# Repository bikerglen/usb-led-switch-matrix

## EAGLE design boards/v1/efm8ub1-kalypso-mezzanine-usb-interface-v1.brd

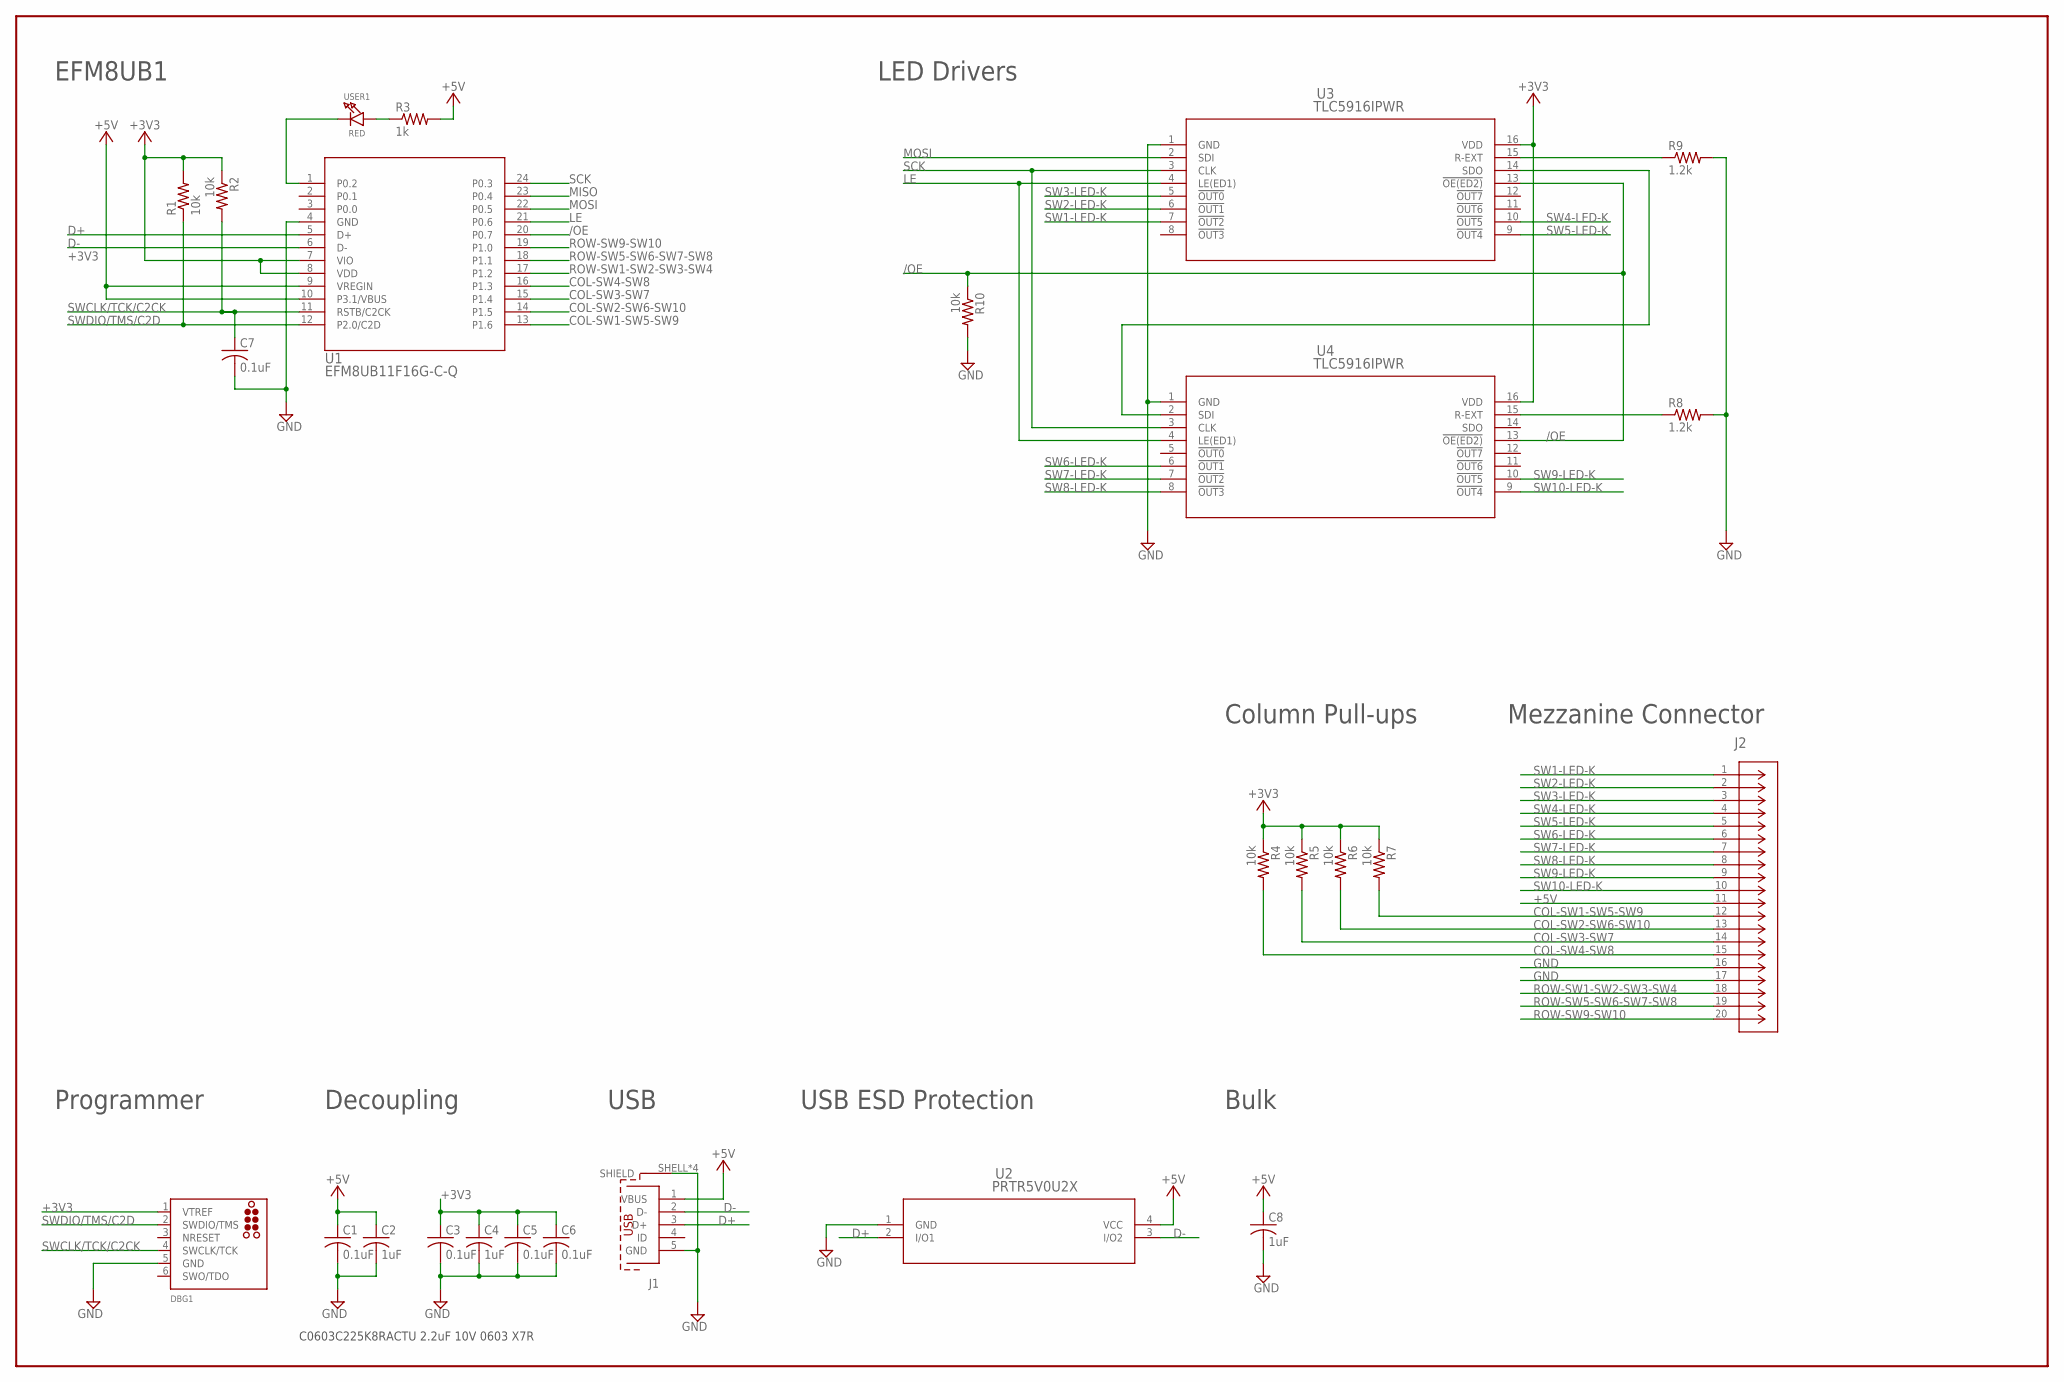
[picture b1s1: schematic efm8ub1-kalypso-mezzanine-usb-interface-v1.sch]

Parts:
C1, C3, C5, C6, C7: 0.1uF; C0603
C2, C4: 1uF; C0603
C8: 1uF; C1210
DBG1: TC2030-CTX-SWD; TC2030-MCP-NL
J1: 629105136821
J2: SLW20S-1C7LF; CON20_1X20_UB_58JF_GLE
R1, R2, R4, R5, R6, R7, R10: 10k; R0603
R3: 1k; R0603
R8, R9: 1.2k; R0603
U1: EFM8UB11F16G-C-Q; QSOP24
U2: PRTR5V0U2X; SOT143B
U3, U4: TLC5916IPWR; PW16_TEX
USER1: RED; CHIPLED_0805_NOOUTLINE

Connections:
+3V3: C3.1, C4.1, C5.1, C6.1, DBG1.1 (VTREF), R1.2, R2.1, R4.1, R5.1, R6.1, R7.1, U1.7 (VIO), U1.8 (VDD), U3.16 (VDD), U4.16 (VDD)
+5V: C1.1, C2.1, C8.1, J1.1 (VBUS), J2.11, R3.2, U1.9 (VREGIN), U1.10 (P3.1/VBUS), U2.4 (VCC)
/OE: R10.1, U1.20 (P0.7), U3.13 (!OE(ED2)), U4.13 (!OE(ED2))
COL-SW1-SW5-SW9: J2.12, R7.2, U1.13 (P1.6)
COL-SW2-SW6-SW10: J2.13, R6.2, U1.14 (P1.5)
COL-SW3-SW7: J2.14, R5.2, U1.15 (P1.4)
COL-SW4-SW8: J2.15, R4.2, U1.16 (P1.3)
D+: J1.3 (D+), U1.5 (D+), U2.2 (I/O1)
D-: J1.2 (D-), U1.6 (D-), U2.3 (I/O2)
GND: C1.2, C2.2, C3.2, C4.2, C5.2, C6.2, C7.2, C8.2, DBG1.5 (GND), J1.5 (GND), J1.SHELL (SHIELD), J1.SHELL1 (SHIELD), J1.SHELL2 (SHIELD), J1.SHELL3 (SHIELD), J2.16, J2.17, R8.2, R9.2, R10.2, U1.4 (GND), U2.1 (GND), U3.1 (GND), U4.1 (GND)
LE: U1.21 (P0.6), U3.4 (LE(ED1)), U4.4 (LE(ED1))
MISO: U1.23 (P0.4)
MOSI: U1.22 (P0.5), U3.2 (SDI)
unnamed: R3.1, USER1.A
unnamed: U3.14 (SDO), U4.2 (SDI)
unnamed: R8.1, U4.15 (R-EXT)
unnamed: R9.1, U3.15 (R-EXT)
NRESET: DBG1.3 (NRESET)
ROW-SW1-SW2-SW3-SW4: J2.18, U1.17 (P1.2)
ROW-SW5-SW6-SW7-SW8: J2.19, U1.18 (P1.1)
ROW-SW9-SW10: J2.20, U1.19 (P1.0)
SCK: U1.24 (P0.3), U3.3 (CLK), U4.3 (CLK)
SW1-LED-K: J2.1, U3.7 (!OUT2)
SW2-LED-K: J2.2, U3.6 (!OUT1)
SW3-LED-K: J2.3, U3.5 (!OUT0)
SW4-LED-K: J2.4, U3.10 (!OUT5)
SW5-LED-K: J2.5, U3.9 (!OUT4)
SW6-LED-K: J2.6, U4.6 (!OUT1)
SW7-LED-K: J2.7, U4.7 (!OUT2)
SW8-LED-K: J2.8, U4.8 (!OUT3)
SW9-LED-K: J2.9, U4.10 (!OUT5)
SW10-LED-K: J2.10, U4.9 (!OUT4)
SWCLK/TCK/C2CK: C7.1, DBG1.4 (SWCLK/TCK), R2.2, U1.11 (RSTB/C2CK)
SWDIO/TMS/C2D: DBG1.2 (SWDIO/TMS), R1.1, U1.12 (P2.0/C2D)
USER1: U1.1 (P0.2), USER1.C

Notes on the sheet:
EFM8UB1
Programmer
Decoupling
USB ESD Protection
C0603C225K8RACTU 2.2uF 10V 0603 X7R
USB
LED Drivers
Column Pull-ups
Mezzanine Connector
Bulk

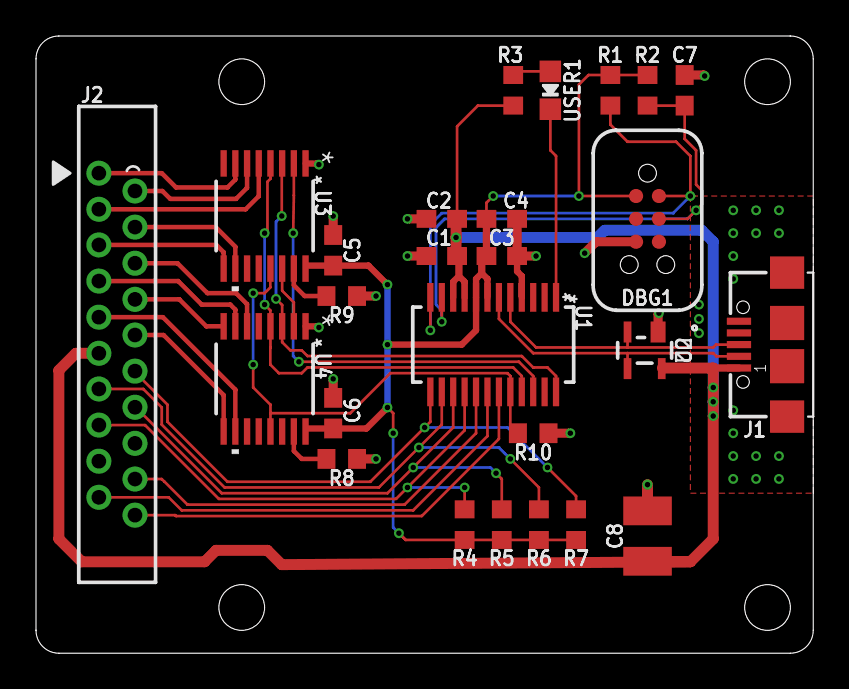
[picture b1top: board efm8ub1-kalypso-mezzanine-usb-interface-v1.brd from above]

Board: 2 copper layers, 43.2 x 34.3 mm, 26 parts (0 on the bottom side), 33 nets.

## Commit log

2020-11-09 initial checkin of PCB design files
2020-11-09 added embedded software
2020-11-09 added linux software

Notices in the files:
parts and their libraries:
InputOutputIO: Copyright: Würth Elektronik
tag-connect: ©2009 ROFA.cz - modified and updated by Robert Darlington ‹rdarlington@gmail.com›
microbuilder: This work is placed in the public domain, and may be freely used for commercial and non-commercial work with the following conditions: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
